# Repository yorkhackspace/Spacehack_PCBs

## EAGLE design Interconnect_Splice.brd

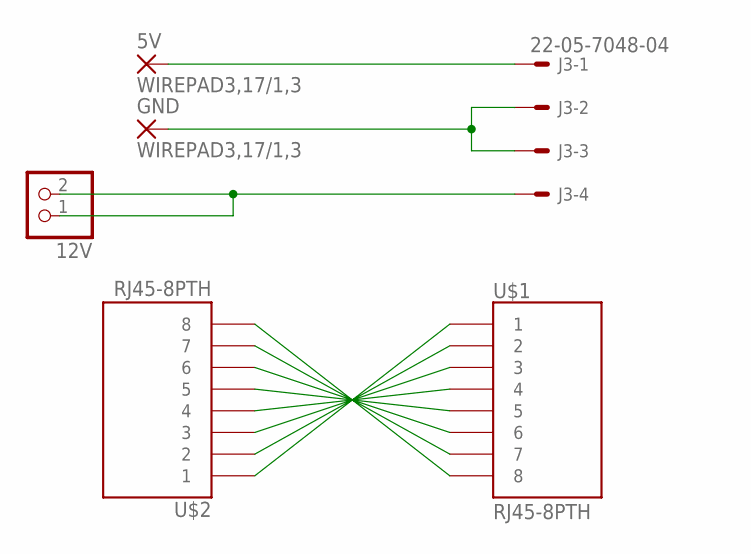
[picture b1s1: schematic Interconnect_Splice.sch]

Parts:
5V: WIREPAD3,17/1,3; 3,17/1,3
12V: PINHD-1X2/90; 1X02/90
GND: WIREPAD3,17/1,3; 3,17/1,3
J3: 22-05-7048-04; 7395-04
U$1, U$2: RJ45-8PTH; RJ45-8

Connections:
GND: GND.1, J3.2, J3.3
unnamed: 5V.1, J3.1
unnamed: 12V.1, 12V.2, J3.4
unnamed: U$1.8, U$2.8
unnamed: U$1.7, U$2.7
unnamed: U$1.6, U$2.6
unnamed: U$1.5, U$2.5
unnamed: U$1.4, U$2.4
unnamed: U$1.3, U$2.3
unnamed: U$1.2, U$2.2
unnamed: U$1.1, U$2.1

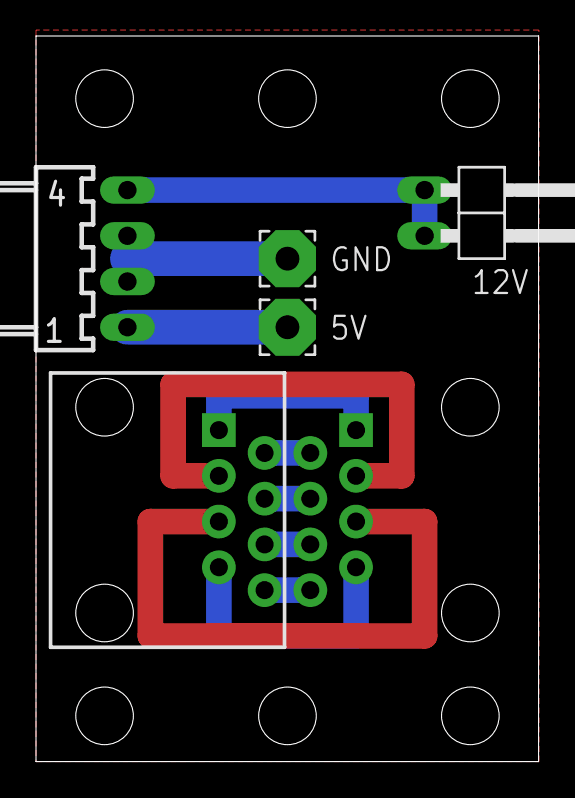
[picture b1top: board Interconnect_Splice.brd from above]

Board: 2 copper layers, 27.9 x 40.3 mm, 6 parts (1 on the bottom side), 11 nets.

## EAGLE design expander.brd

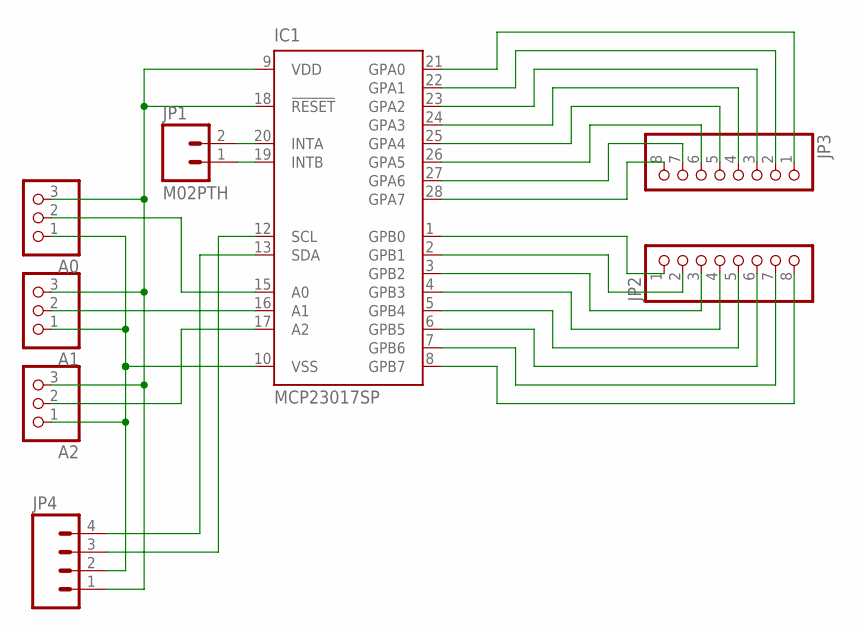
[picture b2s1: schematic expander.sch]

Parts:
A0, A1, A2: PINHD-1X3; 1X03
IC1: MCP23017SP; DIL28-3
JP1: M02PTH; 1X02
JP2, JP3: PINHD-1X8; 1X08
JP4: M04POLAR; MOLEX-1X4

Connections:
GND: A0.1, A1.1, A2.1, IC1.10 (VSS), JP4.2
unnamed: A0.2, IC1.15 (A0)
unnamed: A1.2, IC1.16 (A1)
unnamed: A2.2, IC1.17 (A2)
unnamed: IC1.12 (SCL), JP4.3
unnamed: IC1.13 (SDA), JP4.4
unnamed: IC1.28 (GPA7), JP3.8
unnamed: IC1.1 (GPB0), JP2.1
unnamed: IC1.27 (GPA6), JP3.7
unnamed: IC1.2 (GPB1), JP2.2
unnamed: IC1.26 (GPA5), JP3.6
unnamed: IC1.25 (GPA4), JP3.5
unnamed: IC1.24 (GPA3), JP3.4
unnamed: IC1.23 (GPA2), JP3.3
unnamed: IC1.22 (GPA1), JP3.2
unnamed: IC1.21 (GPA0), JP3.1
unnamed: IC1.3 (GPB2), JP2.3
unnamed: IC1.4 (GPB3), JP2.4
unnamed: IC1.5 (GPB4), JP2.5
unnamed: IC1.6 (GPB5), JP2.6
unnamed: IC1.7 (GPB6), JP2.7
unnamed: IC1.8 (GPB7), JP2.8
unnamed: IC1.19 (INTB), JP1.1
unnamed: IC1.20 (INTA), JP1.2
VCC: A0.3, A1.3, A2.3, IC1.9 (VDD), IC1.18 (!RESET), JP4.1

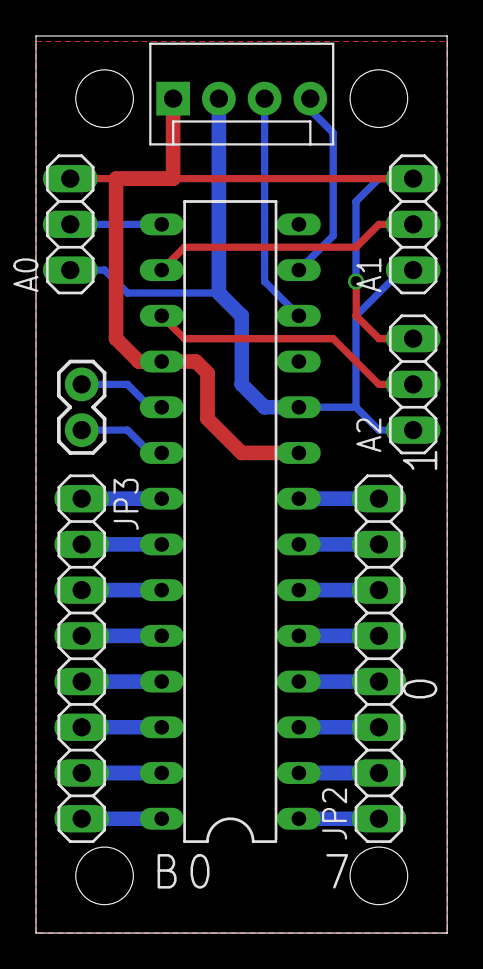
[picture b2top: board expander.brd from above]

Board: 4 copper layers, 22.8 x 49.8 mm, 10 parts (0 on the bottom side), 25 nets.

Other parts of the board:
U$3: JUMP3_DESC_LEFT
U$4: JUMP3_DESC_RIGHT

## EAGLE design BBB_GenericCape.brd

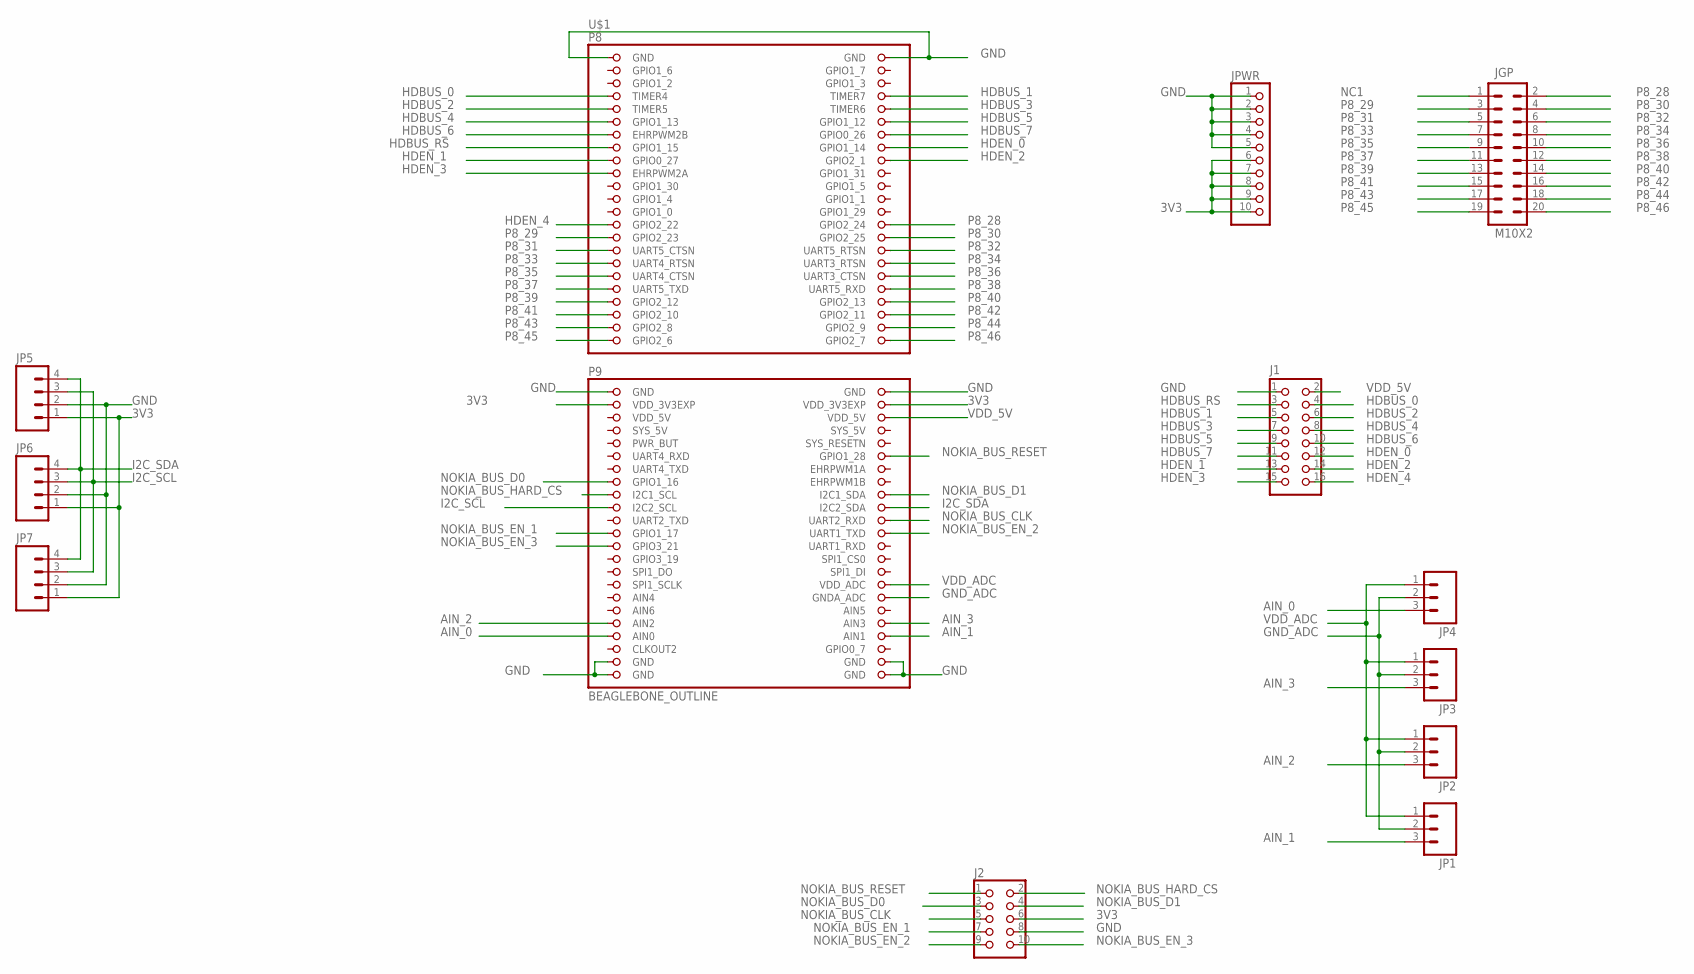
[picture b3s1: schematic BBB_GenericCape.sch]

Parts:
J1: CON_HEADER_2X08SHROUDED; PINSHRD_PTH_2X08
J2: CON_HEADER_2X05-PTH+SHROUDED_A; PINSHRD_PTH_2X05
JGP: M10X2; 2X10
JP1, JP2, JP3, JP4: M03POLAR; MOLEX-1X3
JP5, JP6, JP7: M04POLAR; MOLEX-1X4
JPWR: PINHD-1X10; 1X10
U$1: BEAGLEBONE_OUTLINE; BEAGLEBONE_SHIELD

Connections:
3V3: J2.6, JP5.1, JP6.1, JP7.1, JPWR.6, JPWR.7, JPWR.8, JPWR.9, JPWR.10, U$1.49 (VDD_3V3EXP), U$1.50 (VDD_3V3EXP)
AIN_0: JP4.3, U$1.85 (AIN0)
AIN_1: JP1.3, U$1.86 (AIN1)
AIN_2: JP2.3, U$1.83 (AIN2)
AIN_3: JP3.3, U$1.84 (AIN3)
GND: J1.1, J2.8, JP5.2, JP6.2, JP7.2, JPWR.1, JPWR.2, JPWR.3, JPWR.4, JPWR.5, U$1.1 (GND), U$1.2 (GND), U$1.47 (GND), U$1.48 (GND), U$1.89 (GND), U$1.90 (GND), U$1.91 (GND), U$1.92 (GND)
GND_ADC: JP1.2, JP2.2, JP3.2, JP4.2, U$1.80 (GNDA_ADC)
HDBUS_0: J1.4, U$1.7 (TIMER4)
HDBUS_1: J1.5, U$1.8 (TIMER7)
HDBUS_2: J1.6, U$1.9 (TIMER5)
HDBUS_3: J1.7, U$1.10 (TIMER6)
HDBUS_4: J1.8, U$1.11 (GPIO1_13)
HDBUS_5: J1.9, U$1.12 (GPIO1_12)
HDBUS_6: J1.10, U$1.13 (EHRPWM2B)
HDBUS_7: J1.11, U$1.14 (GPIO0_26)
HDBUS_RS: J1.3, U$1.15 (GPIO1_15)
HDEN_0: J1.12, U$1.16 (GPIO1_14)
HDEN_1: J1.13, U$1.17 (GPIO0_27)
HDEN_2: J1.14, U$1.18 (GPIO2_1)
HDEN_3: J1.15, U$1.19 (EHRPWM2A)
HDEN_4: J1.16, U$1.27 (GPIO2_22)
I2C_SCL: JP5.3, JP6.3, JP7.3, U$1.65 (I2C2_SCL)
I2C_SDA: JP5.4, JP6.4, JP7.4, U$1.66 (I2C2_SDA)
NC1: JGP.1
NOKIA_BUS_CLK: J2.5, U$1.68 (UART2_RXD)
NOKIA_BUS_D0: J2.3, U$1.61 (GPIO1_16)
NOKIA_BUS_D1: J2.4, U$1.64 (I2C1_SDA)
NOKIA_BUS_EN_1: J2.7, U$1.69 (GPIO1_17)
NOKIA_BUS_EN_2: J2.9, U$1.70 (UART1_TXD)
NOKIA_BUS_EN_3: J2.10, U$1.71 (GPIO3_21)
NOKIA_BUS_HARD_CS: J2.2, U$1.63 (I2C1_SCL)
NOKIA_BUS_RESET: J2.1, U$1.58 (GPIO1_28)
P8_28: JGP.2, U$1.28 (GPIO2_24)
P8_29: JGP.3, U$1.29 (GPIO2_23)
P8_30: JGP.4, U$1.30 (GPIO2_25)
P8_31: JGP.5, U$1.31 (UART5_CTSN)
P8_32: JGP.6, U$1.32 (UART5_RTSN)
P8_33: JGP.7, U$1.33 (UART4_RTSN)
P8_34: JGP.8, U$1.34 (UART3_RTSN)
P8_35: JGP.9, U$1.35 (UART4_CTSN)
P8_36: JGP.10, U$1.36 (UART3_CTSN)
P8_37: JGP.11, U$1.37 (UART5_TXD)
P8_38: JGP.12, U$1.38 (UART5_RXD)
P8_39: JGP.13, U$1.39 (GPIO2_12)
P8_40: JGP.14, U$1.40 (GPIO2_13)
P8_41: JGP.15, U$1.41 (GPIO2_10)
P8_42: JGP.16, U$1.42 (GPIO2_11)
P8_43: JGP.17, U$1.43 (GPIO2_8)
P8_44: JGP.18, U$1.44 (GPIO2_9)
P8_45: JGP.19, U$1.45 (GPIO2_6)
P8_46: JGP.20, U$1.46 (GPIO2_7)
SYS_5V: U$1.53 (SYS_5V)
VDD_5V: J1.2, U$1.51 (VDD_5V), U$1.52 (VDD_5V)
VDD_ADC: JP1.1, JP2.1, JP3.1, JP4.1, U$1.78 (VDD_ADC)

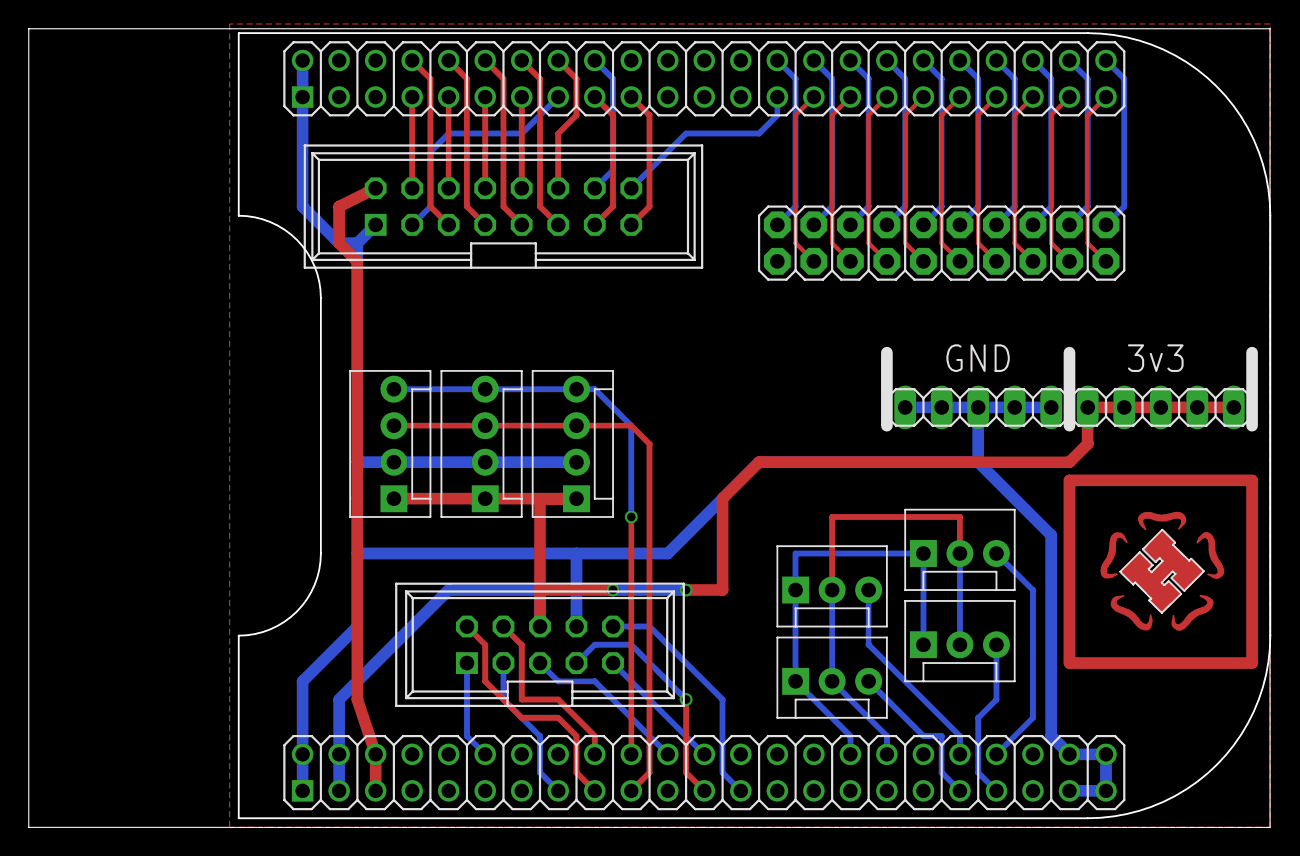
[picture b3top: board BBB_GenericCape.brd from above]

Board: 4 copper layers, 86.3 x 55.5 mm, 13 parts (0 on the bottom side), 52 nets.

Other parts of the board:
U$4: YHSLOGO_SMALL_FANCY

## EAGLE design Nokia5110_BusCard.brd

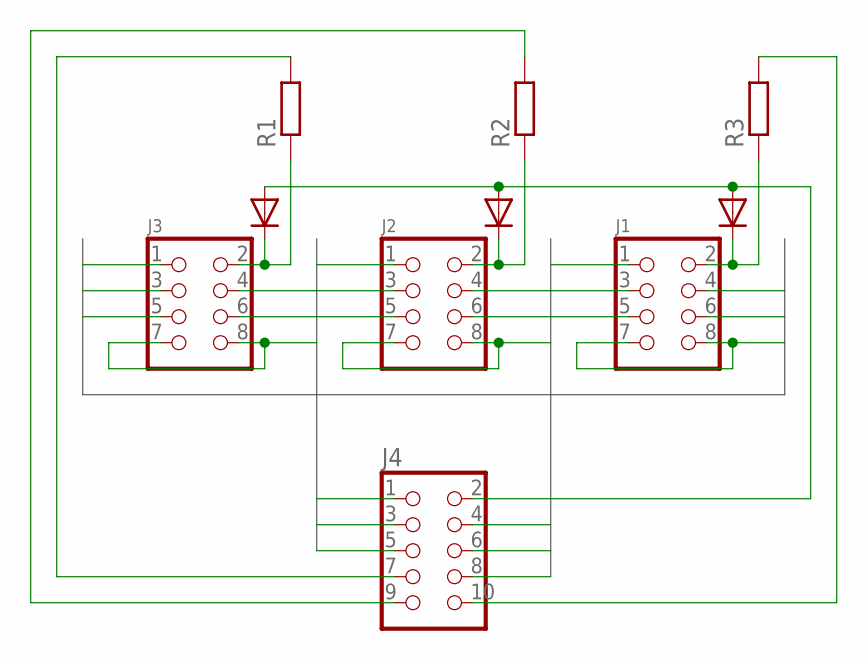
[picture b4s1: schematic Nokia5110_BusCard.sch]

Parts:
D1, D2, D3: 1N4148DO35-7; DO35-7
J1, J2, J3: CON_HEADER_2X04-SHRD_PTH; PINSHRD_PTH_2X04
J4: CON_HEADER_2X05-PTH+SHROUDED_A; PINSHRD_PTH_2X05
R1, R2, R3: R-EU_0207/10; 0207/10

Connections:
unnamed: D3.C, J3.2, R1.1
unnamed: D2.C, J2.2, R2.1
unnamed: D1.C, J1.2, R3.1
unnamed: D1.A, D2.A, D3.A, J4.2
unnamed: J4.7, R1.2
unnamed: J4.9, R2.2
unnamed: J4.10, R3.2
NOKIABUS1: J1.1, J2.1, J3.1, J4.1
NOKIABUS3: J1.3, J2.3, J3.3, J4.3
NOKIABUS4: J1.4, J2.4, J3.4, J4.4
NOKIABUS5: J1.5, J2.5, J3.5, J4.5
NOKIABUS6: J1.6, J2.6, J3.6, J4.6
NOKIABUS8: J1.7, J1.8, J2.7, J2.8, J3.7, J3.8, J4.8

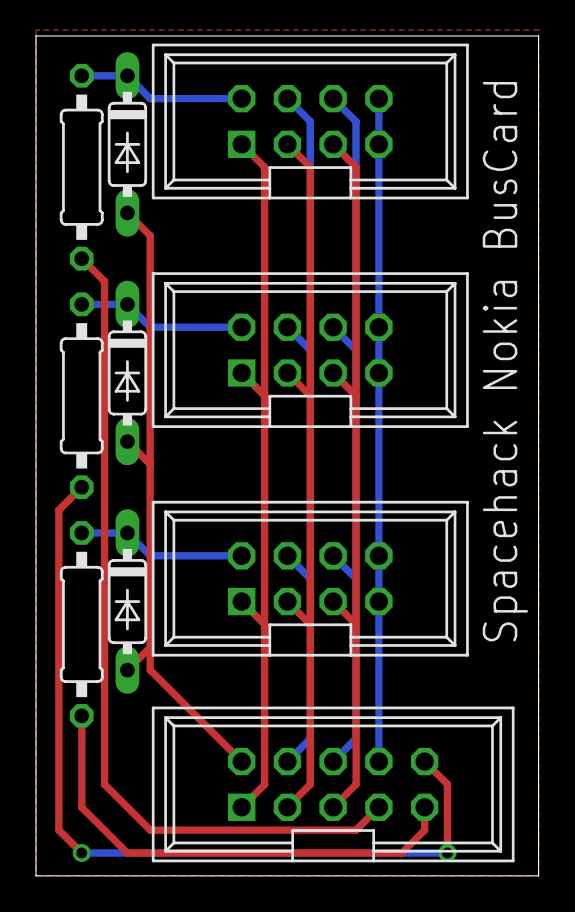
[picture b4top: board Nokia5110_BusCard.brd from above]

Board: 2 copper layers, 27.9 x 46.7 mm, 10 parts (0 on the bottom side), 13 nets.

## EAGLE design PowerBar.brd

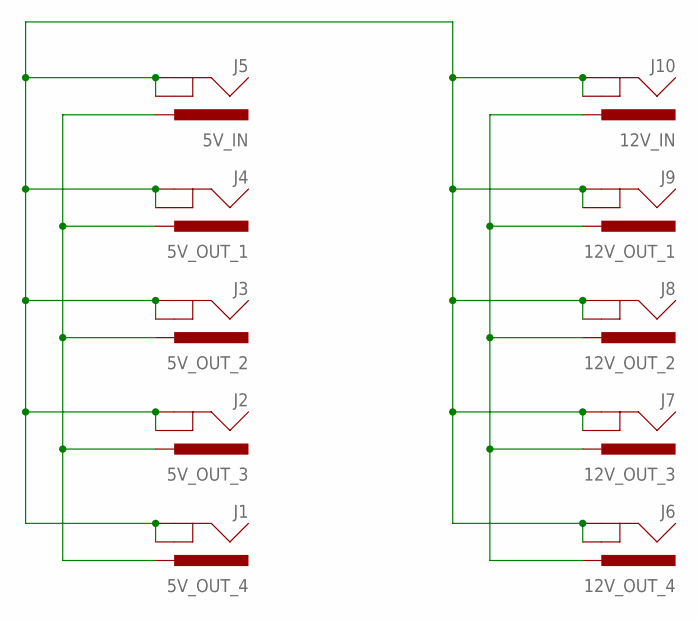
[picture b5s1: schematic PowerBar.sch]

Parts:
J1: 5V_OUT_4; POWER_JACK_PTH
J2: 5V_OUT_3; POWER_JACK_PTH
J3: 5V_OUT_2; POWER_JACK_PTH
J4: 5V_OUT_1; POWER_JACK_PTH
J5: 5V_IN; POWER_JACK_PTH
J6: 12V_OUT_4; POWER_JACK_PTH
J7: 12V_OUT_3; POWER_JACK_PTH
J8: 12V_OUT_2; POWER_JACK_PTH
J9: 12V_OUT_1; POWER_JACK_PTH
J10: 12V_IN; POWER_JACK_PTH

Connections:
unnamed: J1.GND, J1.GNDBREAK, J2.GND, J2.GNDBREAK, J3.GND, J3.GNDBREAK, J4.GND, J4.GNDBREAK, J5.GND, J5.GNDBREAK, J6.GND, J6.GNDBREAK, J7.GND, J7.GNDBREAK, J8.GND, J8.GNDBREAK, J9.GND, J9.GNDBREAK, J10.GND, J10.GNDBREAK
unnamed: J1.PWR, J2.PWR, J3.PWR, J4.PWR, J5.PWR
unnamed: J6.PWR, J7.PWR, J8.PWR, J9.PWR, J10.PWR

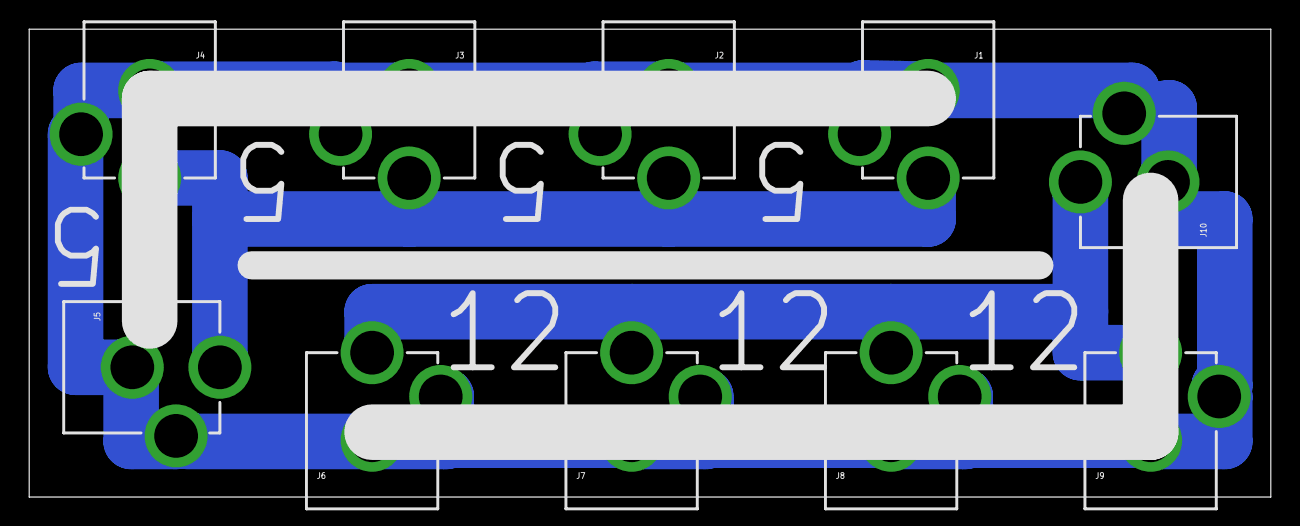
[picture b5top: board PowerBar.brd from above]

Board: 2 copper layers, 85.1 x 32.1 mm, 10 parts (0 on the bottom side), 3 nets.

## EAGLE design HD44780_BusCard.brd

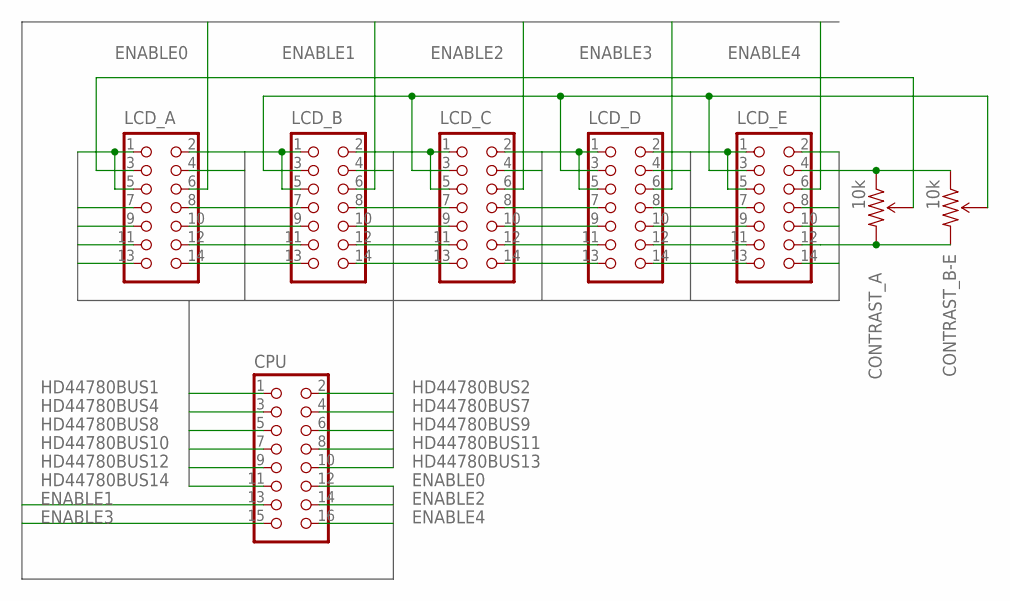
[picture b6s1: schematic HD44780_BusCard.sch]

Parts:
CONTRAST_A: 10k; 3386U
CONTRAST_B-E: 10k; 3386U
CPU: CON_HEADER_2X08SHROUDED; PINSHRD_PTH_2X08
LCD_A: CON_HEADER_2X07-PTH-SHROUDED; PINSHRD_PTH_2X07
LCD_B: CON_HEADER_2X07-PTH-SHROUDED; PINSHRD_PTH_2X07
LCD_C: CON_HEADER_2X07-PTH-SHROUDED; PINSHRD_PTH_2X07
LCD_D: CON_HEADER_2X07-PTH-SHROUDED; PINSHRD_PTH_2X07
LCD_E: CON_HEADER_2X07-PTH-SHROUDED; PINSHRD_PTH_2X07

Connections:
ENABLE0: CPU.12, LCD_A.6
ENABLE1: CPU.13, LCD_B.6
ENABLE2: CPU.14, LCD_C.6
ENABLE3: CPU.15, LCD_D.6
ENABLE4: CPU.16, LCD_E.6
HD44780BUS1: CONTRAST_A.1 (CCW), CONTRAST_B-E.1 (CCW), CPU.1, LCD_A.1, LCD_A.5, LCD_B.1, LCD_B.5, LCD_C.1, LCD_C.5, LCD_D.1, LCD_D.5, LCD_E.1, LCD_E.5
HD44780BUS2: CONTRAST_A.3 (CW), CONTRAST_B-E.3 (CW), CPU.2, LCD_A.2, LCD_B.2, LCD_C.2, LCD_D.2, LCD_E.2
HD44780BUS4: CPU.3, LCD_A.4, LCD_B.4, LCD_C.4, LCD_D.4, LCD_E.4
HD44780BUS7: CPU.4, LCD_A.7, LCD_B.7, LCD_C.7, LCD_D.7, LCD_E.7
HD44780BUS8: CPU.5, LCD_A.8, LCD_B.8, LCD_C.8, LCD_D.8, LCD_E.8
HD44780BUS9: CPU.6, LCD_A.9, LCD_B.9, LCD_C.9, LCD_D.9, LCD_E.9
HD44780BUS10: CPU.7, LCD_A.10, LCD_B.10, LCD_C.10, LCD_D.10, LCD_E.10
HD44780BUS11: CPU.8, LCD_A.11, LCD_B.11, LCD_C.11, LCD_D.11, LCD_E.11
HD44780BUS12: CPU.9, LCD_A.12, LCD_B.12, LCD_C.12, LCD_D.12, LCD_E.12
HD44780BUS13: CPU.10, LCD_A.13, LCD_B.13, LCD_C.13, LCD_D.13, LCD_E.13
HD44780BUS14: CPU.11, LCD_A.14, LCD_B.14, LCD_C.14, LCD_D.14, LCD_E.14
unnamed: CONTRAST_A.2 (WIPER), LCD_A.3
unnamed: CONTRAST_B-E.2 (WIPER), LCD_B.3, LCD_C.3, LCD_D.3, LCD_E.3

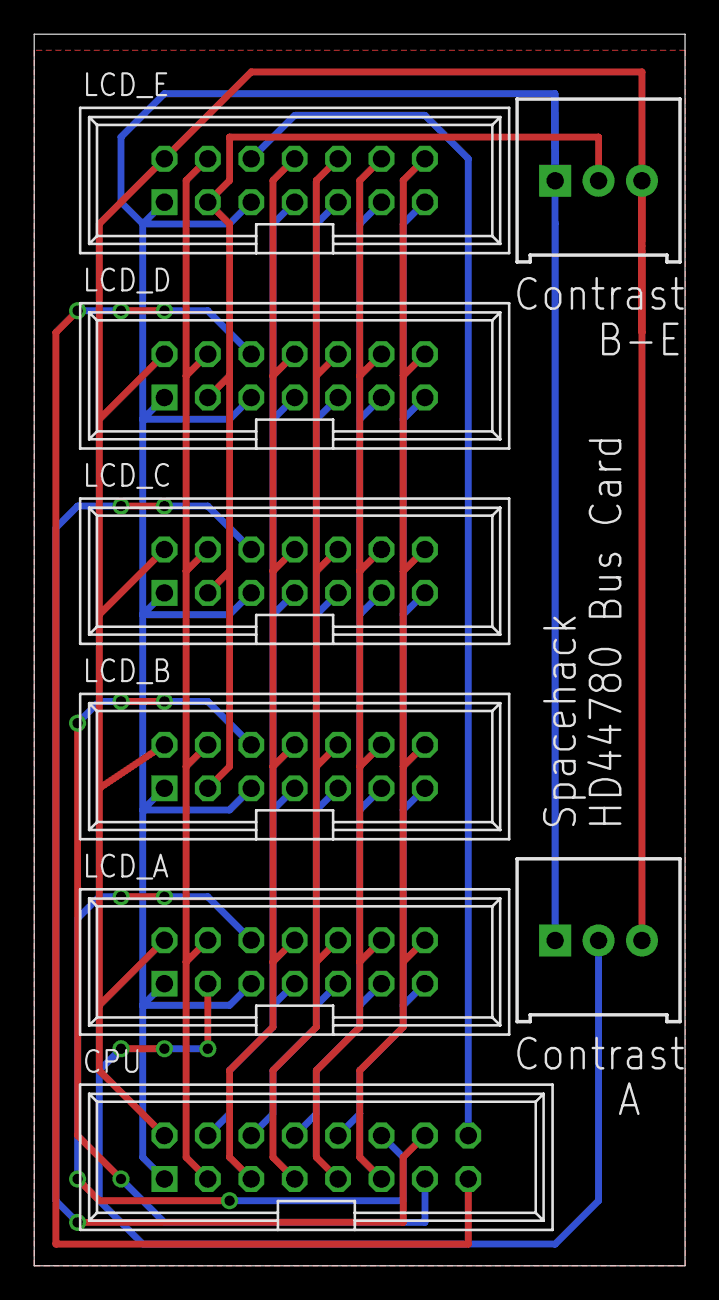
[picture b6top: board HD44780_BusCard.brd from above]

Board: 2 copper layers, 38.1 x 72.1 mm, 8 parts (0 on the bottom side), 18 nets.

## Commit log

2015-02-11 fixed bbb cape issue, did something with cable splice
2015-02-11 Added lots of other files
2015-02-11 added stls
2015-02-11 added spacer mesh

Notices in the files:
parts and their libraries:
SparkFun-Connectors: Licensing: CC v3.0 Share-Alike You are welcome to use this library for commercial purposes.
